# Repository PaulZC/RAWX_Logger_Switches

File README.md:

# RAWX_Logger_Switches

A switch PCB for the [ZED-F9P_FeatherWing](https://github.com/PaulZC/ZED-F9P_FeatherWing) and
[ZED-F9P_FeatherWing_USB](https://github.com/PaulZC/ZED-F9P_FeatherWing_USB)

Contains:

### Three slide switches:
- ON/OFF power control (pulls the EN line low to disable the 3.3V regulators on the FeatherWing and the Adalogger)
- Base/Rover mode (pulls A0 low for Base mode, leaves it floating for Rover mode)
- Survey_In mode (pulls A3 low to enable Survey_In (RTCM) mode when in Base mode)

### Two push button switches:
- EVENT (pulls A2 (ZED-F9P EXTINT) pin low to create a TIM_TM2 event message)
- STOP (pulls A1 low to stop logging and close the log file)

### NeoPixel:
- Indicates the status of the Logger

Based extensively on the Adafruit Feather(Wing) product range

The Eagle files are available in the [Eagle folder](https://github.com/PaulZC/RAWX_Logger_Switches/tree/master/Eagle)

The schematic is available [here](https://github.com/PaulZC/RAWX_Logger_Switches/blob/master/img/Schematic.PNG)

## BOM

- The ON/OFF, BASE/ROVER and SURVEY_IN slide switches are: E-Switch part EG1218 (Farnell / Element14 part 2787232)
- The EVENT and STOP push switches are: e.g. Multicomp MCDTS6-1N 160gf (Farnell / Element14 part 9471685)
- LED1 is a Sparkfun / Worldsemi WS2812B NeoPixel (Mouser part 474-COM-13667)
- LED2 is an 0805 (2.0x1.25mm) red LED: e.g. Wurth Electronik 150080RS75000 (Farnell / Element14 part 2322077)
- R1 is a generic 0805 or 0603 1K resistor: e.g. Multicomp MCWR06X1001FTL (Farnell / Element14 part 2447272)
- C1 and C2 are generic 0603 0.1uF (100nF) ceramic capacitors: e.g. Murata GRM188R71H104JA93D (Farnell / Element14 part 2688523)

LED2 and R1 are optional if you are using the NeoPixel

## Acknowledgements

This project would not have been possible without the open source designs kindly provided by Adafruit.

Adafruit invests time and resources providing this open source design, please support Adafruit and open-source hardware by purchasing products from Adafruit!

## Licence

This project is distributed under a Creative Commons Attribution + Share-alike (BY-SA) licence.
Please refer to section 5 of the licence for the "Disclaimer of Warranties and Limitation of Liability".

Enjoy!

**_Paul_**

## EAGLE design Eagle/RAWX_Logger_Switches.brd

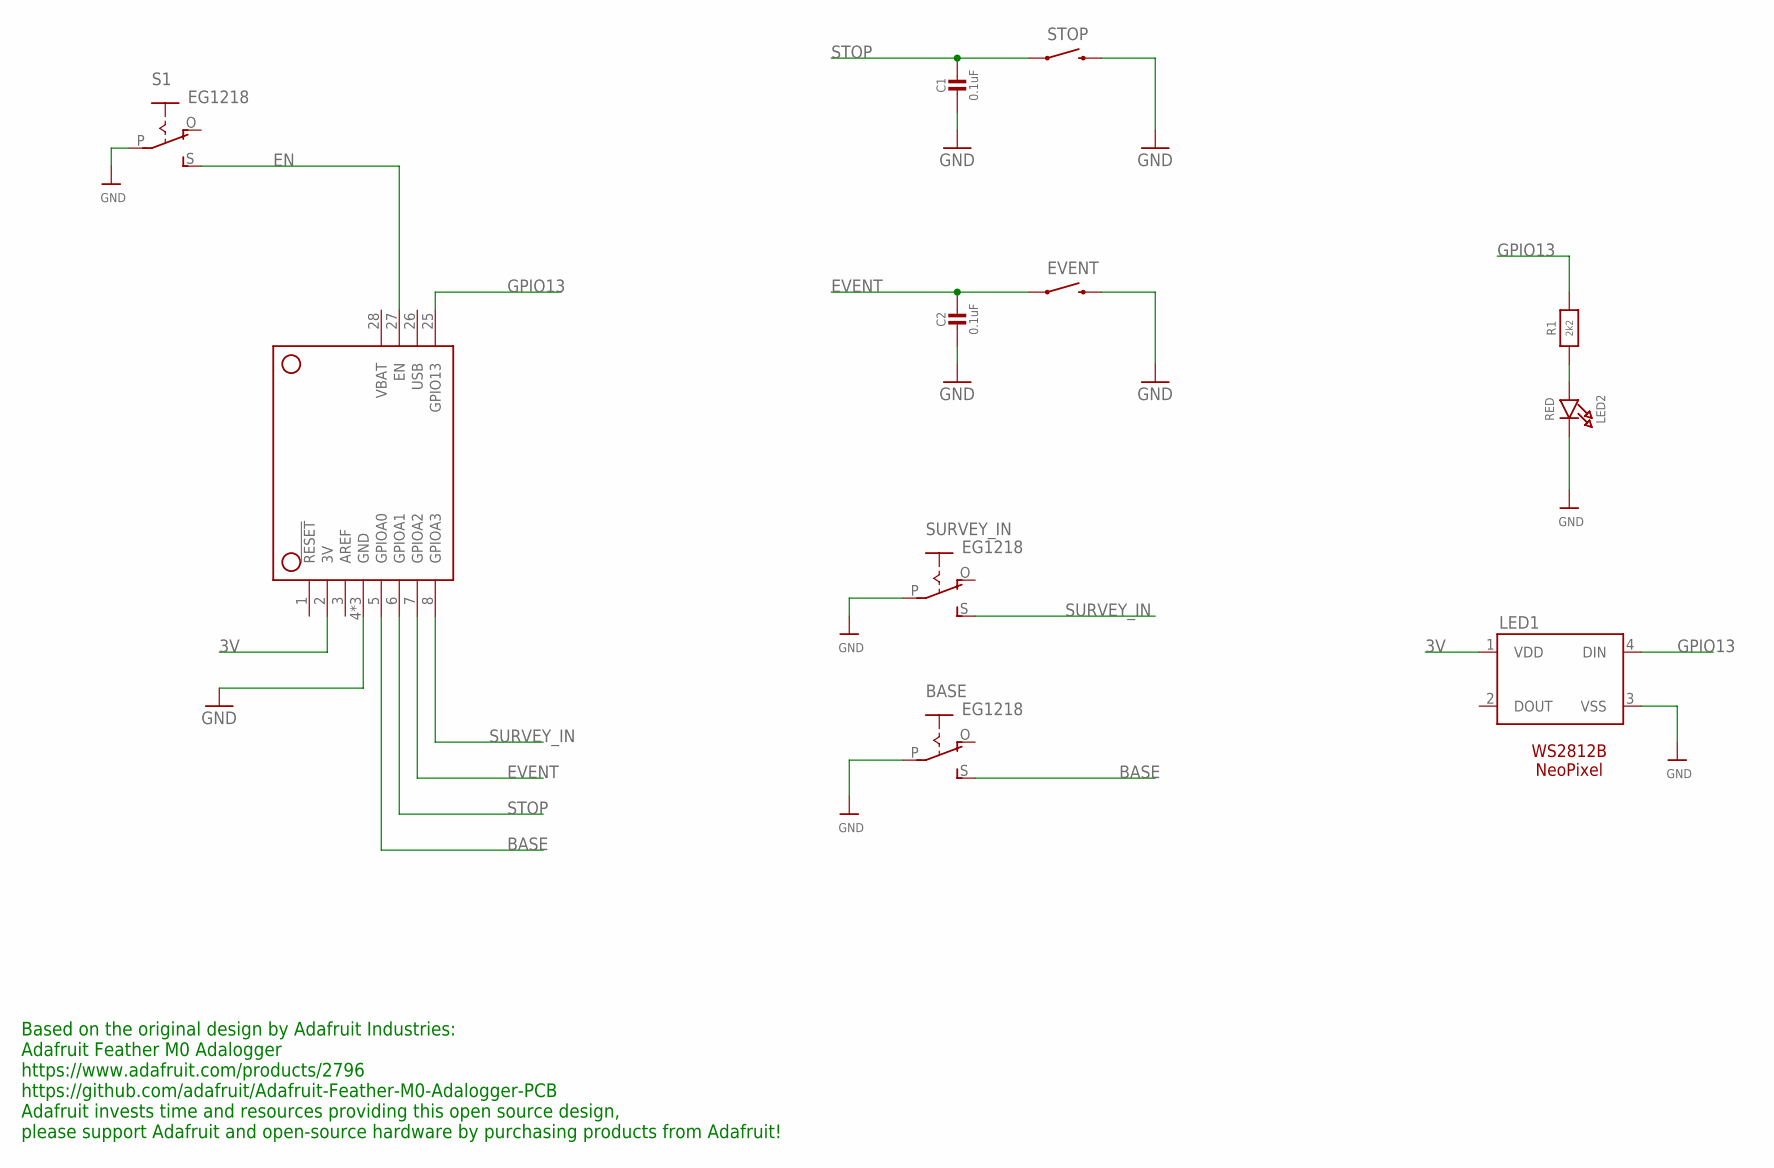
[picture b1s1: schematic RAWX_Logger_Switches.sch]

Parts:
BASE: EG1218
C1, C2: 0.1uF; 0603-NO
EVENT: SWITCH-MOMENTARY-2PTH; TACTILE-PTH
LED1: WS2812B
LED2: RED; CHIPLED_0805_NOOUTLINE
MS1: MICROBUILDER_FEATHERWING_EN_SWITCH
R1: 2k2; 0805-NO
S1: EG1218
STOP: SWITCH-MOMENTARY-2PTH; TACTILE-PTH
SURVEY_IN: EG1218

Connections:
3V: LED1.1 (VDD), MS1.2 (3V)
BASE: BASE.S, MS1.5 (GPIOA0)
EN: MS1.27 (EN), S1.S
EVENT: C2.1, EVENT.1, MS1.7 (GPIOA2)
GND: BASE.P, C1.2, C2.2, EVENT.3 (2), LED1.3 (VSS), LED2.C, MS1.4 (GND), MS1.P$1 (GND), MS1.P$2 (GND), S1.P, STOP.3 (2), SURVEY_IN.P
GPIO13: LED1.4 (DIN), MS1.25 (GPIO13), R1.2
unnamed: LED2.A, R1.1
STOP: C1.1, MS1.6 (GPIOA1), STOP.1
SURVEY_IN: MS1.8 (GPIOA3), SURVEY_IN.S

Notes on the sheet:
WS2812B NeoPixel
Based on the original design by Adafruit Industries: Adafruit Feather M0 Adalogger https://www.adafruit.com/products/2796 https://github.com/adafruit/Adafruit-Feather-M0-Adalogger-PCB Adafruit invests time and resources providing this open source design, please support Adafruit and open-source hard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

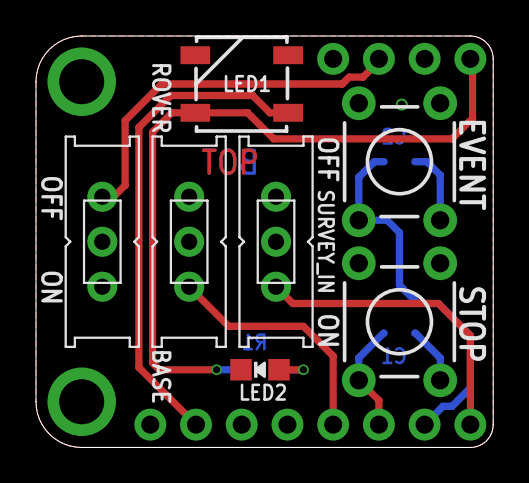
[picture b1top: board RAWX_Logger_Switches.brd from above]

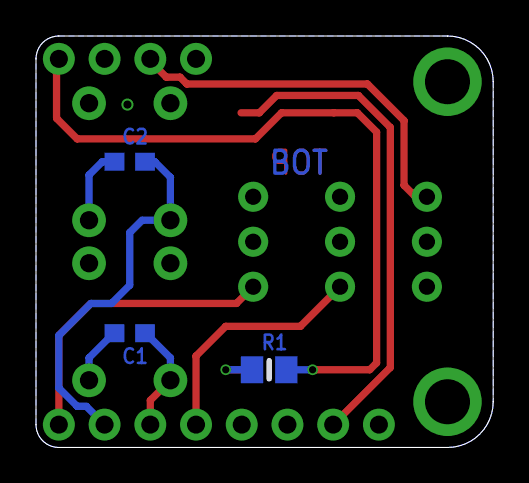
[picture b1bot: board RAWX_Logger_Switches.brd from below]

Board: 2 copper layers, 25.4 x 22.9 mm, 11 parts (3 on the bottom side), 9 nets.

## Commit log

2019-06-08 Resized the images
2019-06-08 Minor corrections
2019-06-12 Updated the switch positions
2019-06-27 Added the as-built photos
2019-06-27 Corrected the image links

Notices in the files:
parts and their libraries:
SparkFun-LED: Licensing: Creative Commons ShareAlike 4.0 International - https://creativecommons.org/licenses/by-sa/4.0
